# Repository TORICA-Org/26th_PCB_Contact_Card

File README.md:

# 26th_PCB_Contact_Card
基板名刺用リポジトリ

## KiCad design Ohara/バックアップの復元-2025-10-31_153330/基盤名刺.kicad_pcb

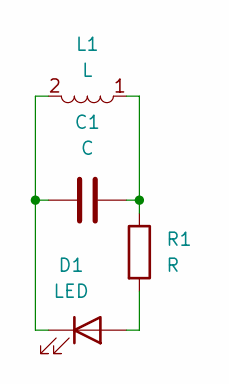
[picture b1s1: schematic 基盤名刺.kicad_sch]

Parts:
C1: C; C_0603_1608Metric_Pad1.08x0.95mm_HandSolder
D1: LED; LED_0603_1608Metric_Pad1.05x0.95mm_HandSolder
L1: L; NFC_COIL_36.7x36.7_3uH
R1: R; R_0603_1608Metric_Pad0.98x0.95mm_HandSolder

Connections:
unnamed: C1.2, L1.1, R1.1
unnamed: D1.2 (A), R1.2
unnamed: C1.1, D1.1 (K), L1.2

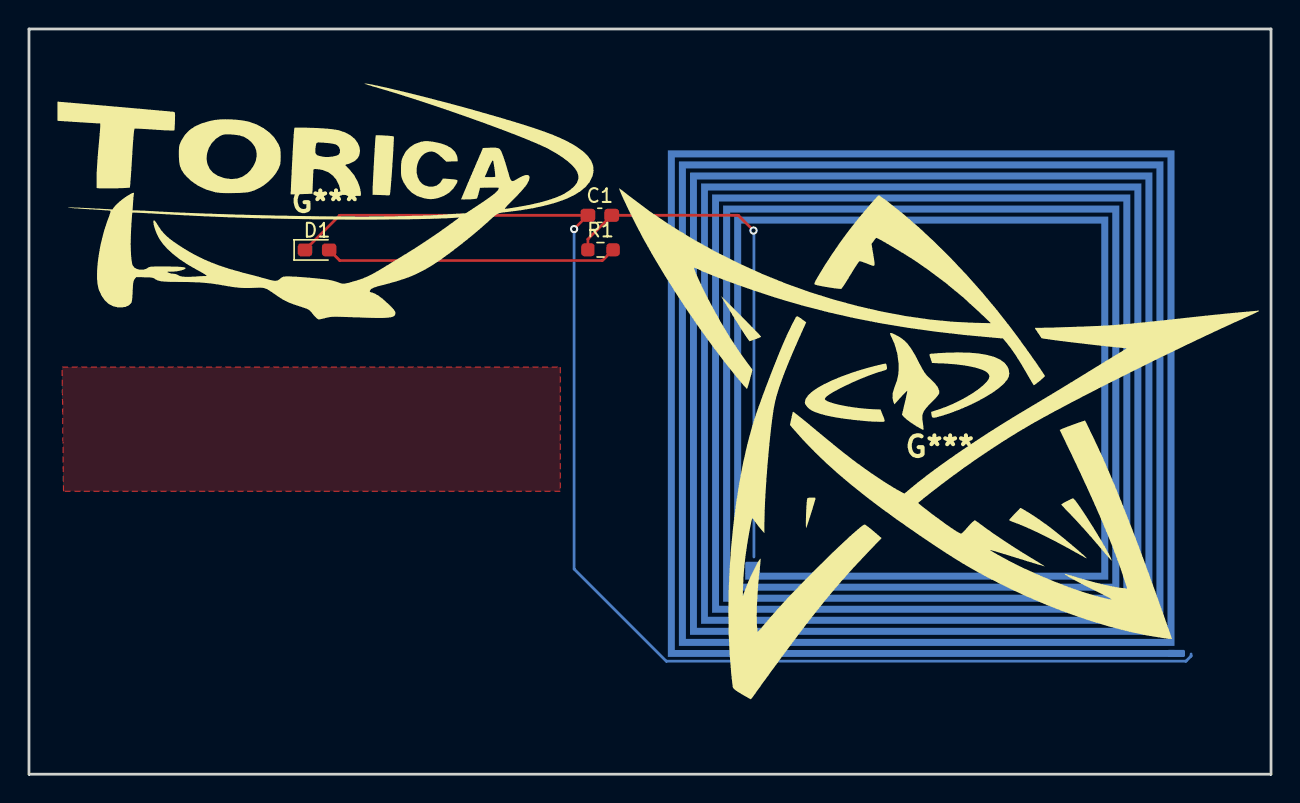
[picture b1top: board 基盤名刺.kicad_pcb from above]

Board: 2 copper layers, 90.0 x 54.0 mm, 4 parts (1 on the bottom side), 3 nets.

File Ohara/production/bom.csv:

Designator,Footprint,Quantity,Value,LCSC Part #
C1,0603,1,C,
D1,0603,1,LED,
L1,NFC_COIL_36.7x36.7_3uH,1,L,
R1,0603,1,R,

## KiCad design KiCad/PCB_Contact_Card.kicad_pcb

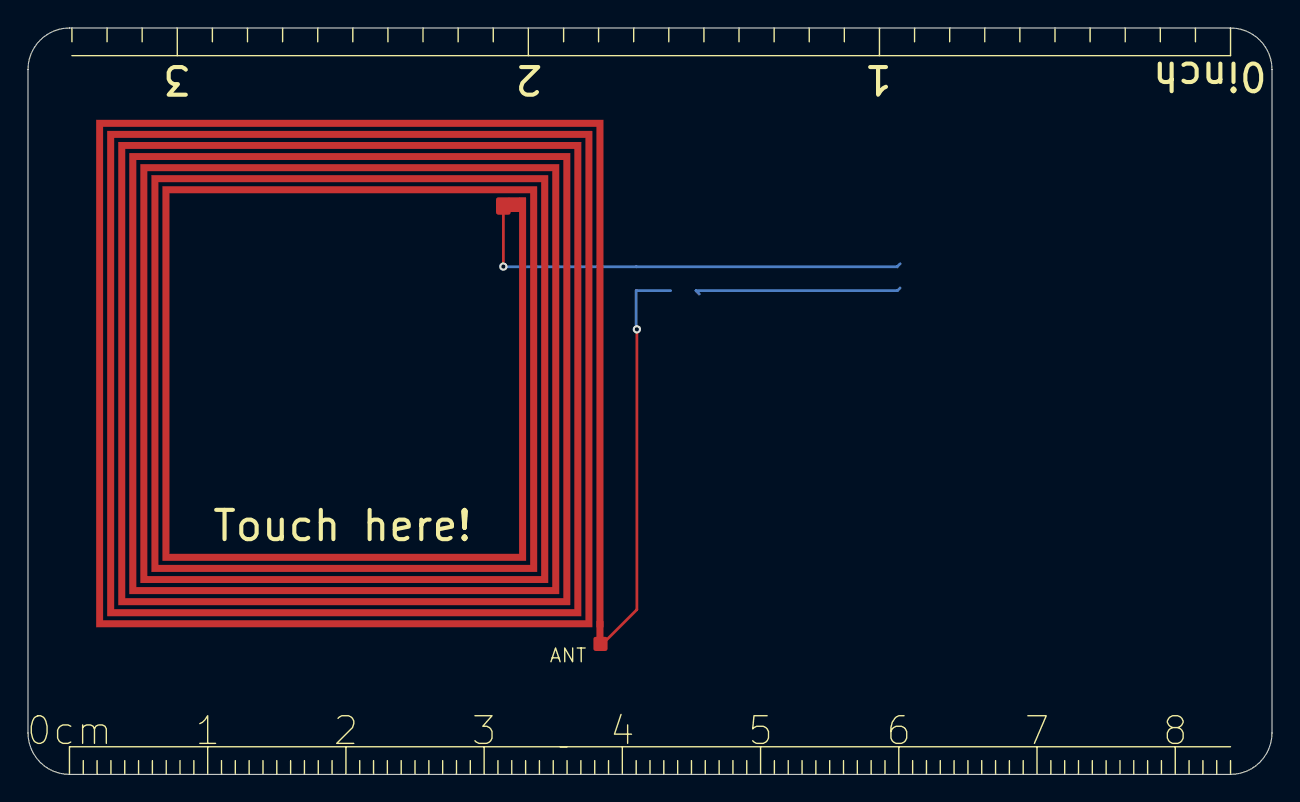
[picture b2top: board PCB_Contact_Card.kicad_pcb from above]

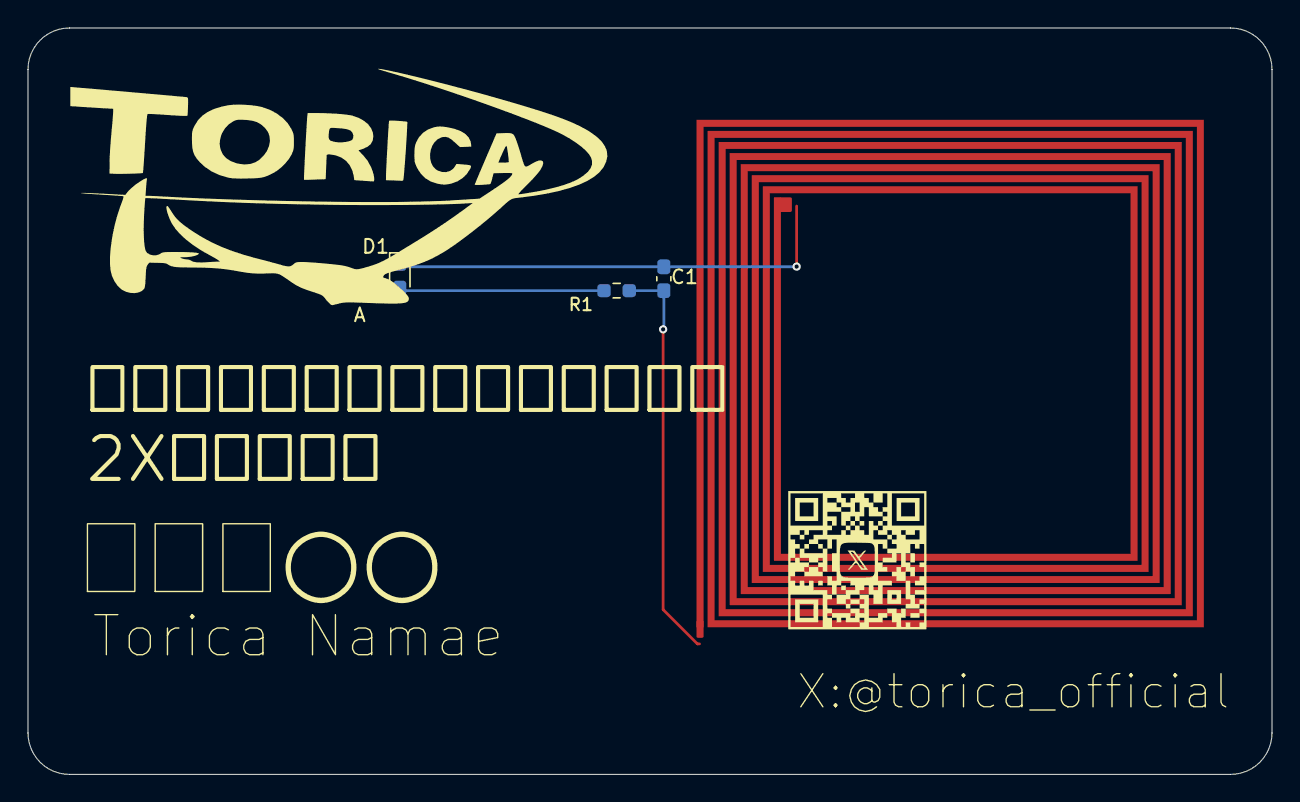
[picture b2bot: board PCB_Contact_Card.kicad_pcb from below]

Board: 2 copper layers, 90.0 x 54.0 mm, 4 parts (3 on the bottom side), 3 nets.

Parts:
ANT: L; NFC_COIL_36.7x36.7_3uH
C1: C; C_0603_1608Metric_Pad1.08x0.95mm_HandSolder
D1: LED; LED_0603_1608Metric_Pad1.05x0.95mm_HandSolder
R1: R; R_0603_1608Metric_Pad0.98x0.95mm_HandSolder

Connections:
unnamed: ANT.2, C1.2, R1.1
unnamed: D1.2 (A), R1.2
unnamed: ANT.1, C1.1, D1.1 (K)

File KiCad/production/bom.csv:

Designator,Footprint,Quantity,Value,LCSC Part #
ANT,NFC_COIL_36.7x36.7_3uH,1,L,
C1,0603,1,C,
D1,0603,1,LED,
R1,0603,1,R,

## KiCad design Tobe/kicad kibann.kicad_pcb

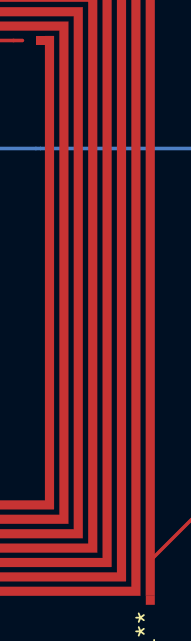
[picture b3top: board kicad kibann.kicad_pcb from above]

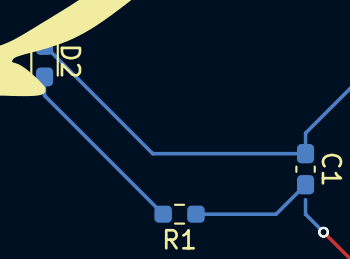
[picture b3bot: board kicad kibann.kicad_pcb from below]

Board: 2 copper layers, 4 parts (3 on the bottom side), 3 nets.

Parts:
C1: C; C_0603_1608Metric_Pad1.08x0.95mm_HandSolder
D2: LED; LED_0603_1608Metric_Pad1.05x0.95mm_HandSolder
L**: 3.00 uH; NFC_COIL_36.7x36.7_3uH
R1: R; R_0603_1608Metric_Pad0.98x0.95mm_HandSolder

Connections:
unnamed: C1.2, R1.1
unnamed: D2.2 (A), R1.2
unnamed: C1.1, D2.1 (K)

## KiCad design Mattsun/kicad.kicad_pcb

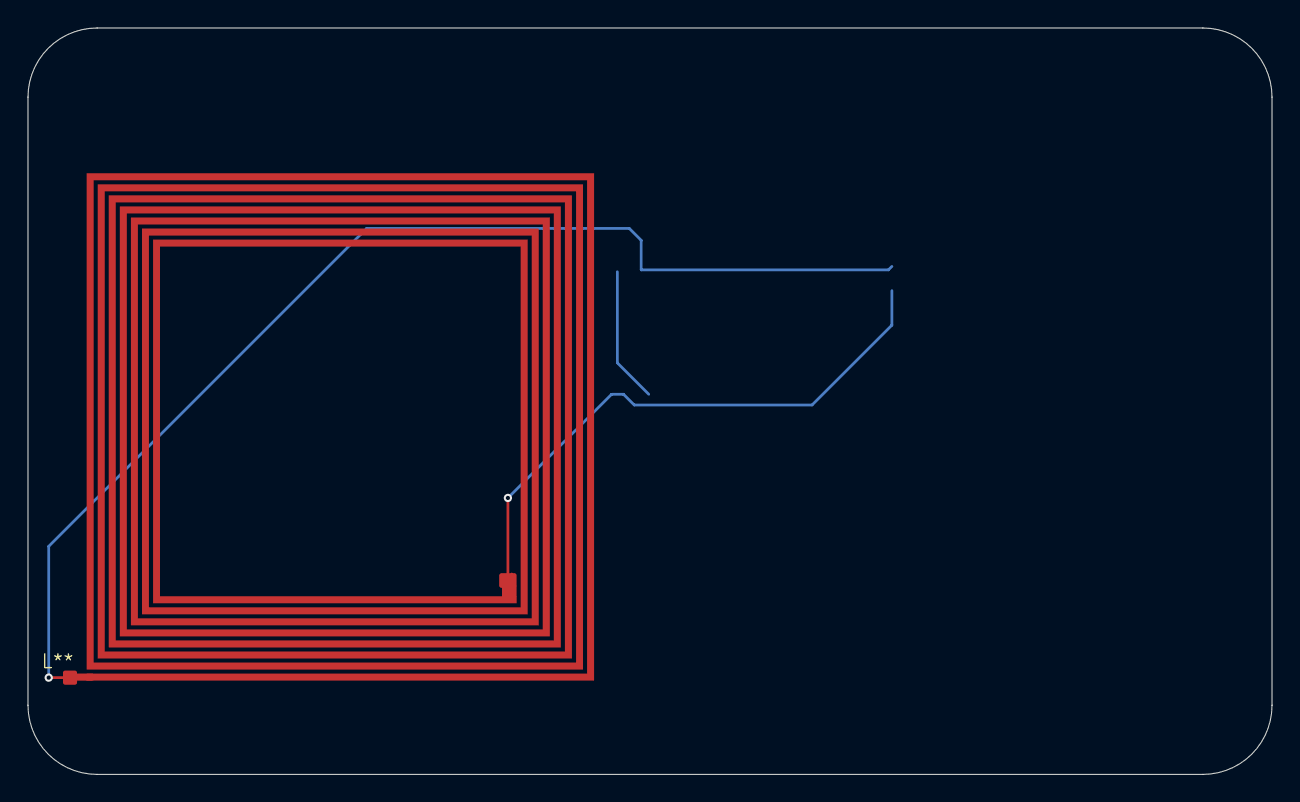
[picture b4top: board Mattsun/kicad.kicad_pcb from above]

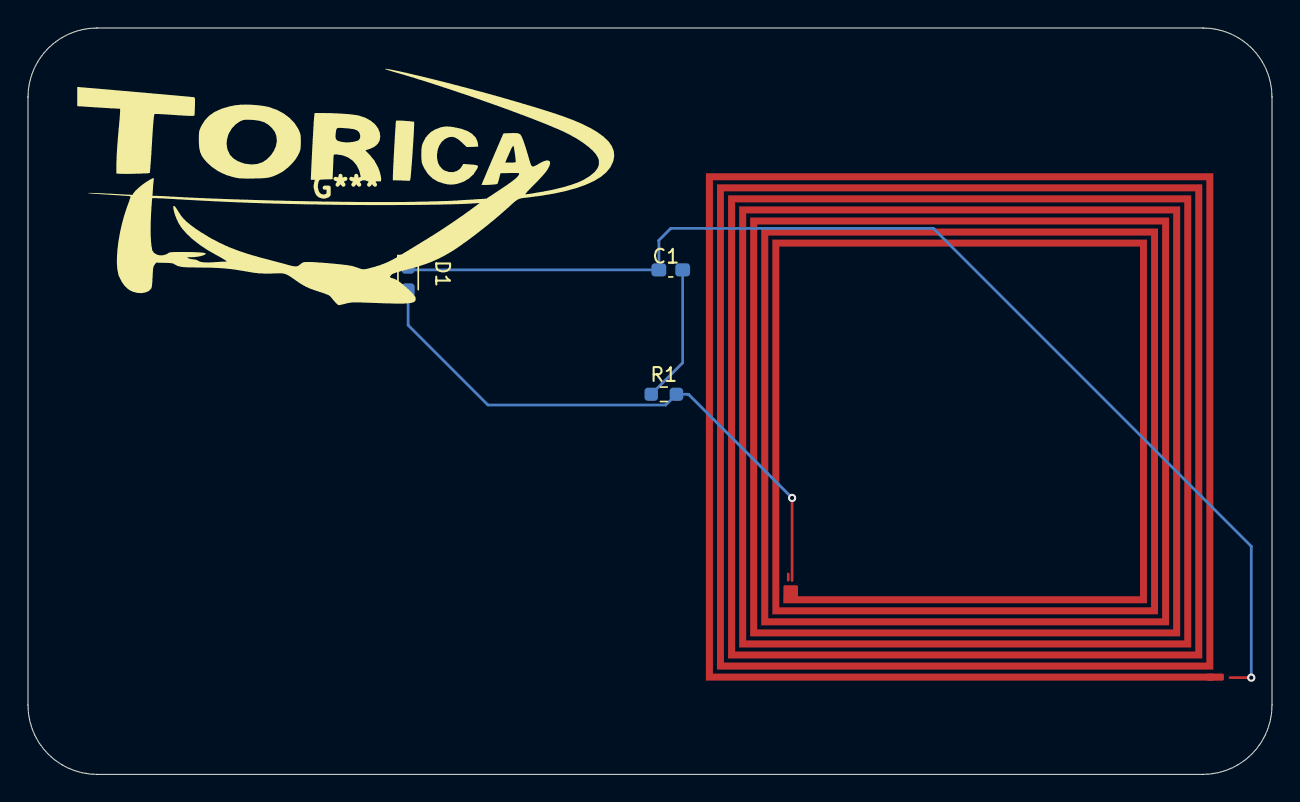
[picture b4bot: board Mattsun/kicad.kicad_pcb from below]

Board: 2 copper layers, 90.0 x 54.0 mm, 4 parts (3 on the bottom side), 3 nets.

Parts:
C1: C; C_0603_1608Metric_Pad1.08x0.95mm_HandSolder
D1: LED; LED_0603_1608Metric_Pad1.05x0.95mm_HandSolder
L**: 3.00 uH; NFC_COIL_36.7x36.7_3uH
R1: R; R_0603_1608Metric_Pad0.98x0.95mm_HandSolder

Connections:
unnamed: C1.2, R1.1
unnamed: D1.2 (A), L**.1, R1.2
unnamed: C1.1, D1.1 (K), L**.2

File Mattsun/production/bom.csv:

Designator,Footprint,Quantity,Value,LCSC Part #
C1,0603,1,C,
D1,0603,1,LED,
R1,0603,1,R,

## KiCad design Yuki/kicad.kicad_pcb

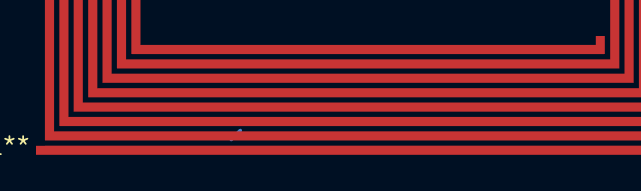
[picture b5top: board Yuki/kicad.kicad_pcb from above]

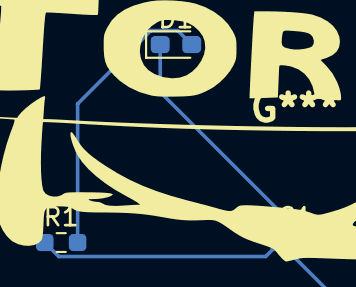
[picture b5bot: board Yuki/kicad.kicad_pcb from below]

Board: 2 copper layers, 4 parts (3 on the bottom side), 3 nets.

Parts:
C1: C; C_0603_1608Metric_Pad1.08x0.95mm_HandSolder
D1: LED; LED_0603_1608Metric_Pad1.05x0.95mm_HandSolder
L**: 3.00 uH; NFC_COIL_36.7x36.7_3uH
R1: R; R_0603_1608Metric_Pad0.98x0.95mm_HandSolder

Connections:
unnamed: C1.1, R1.1
unnamed: D1.2 (A), R1.2
unnamed: C1.2, D1.1 (K)

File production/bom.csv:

Designator,Footprint,Quantity,Value,LCSC Part #
C1,0603,1,C,
D1,0603,1,LED,
R1,0603,1,R,

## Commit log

2025-08-29 基盤名刺1日目
2025-08-29 基板名刺1日目
2025-08-29 基盤名刺途中
2025-08-29 基盤名刺仮
2025-09-02 footprint fixed
    アンテナのフットプリントのバク修正
2025-09-10 根澤優輝 基盤名刺
2025-09-10 kibannmeisi
2025-09-10 基盤名刺 松
2025-11-07 onefile
2025-11-07 confirm
2025-11-08 switch to Ohara
2025-11-08 Ohara's PCB problem was solved
